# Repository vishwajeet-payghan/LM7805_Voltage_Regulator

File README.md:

**LM7805 5V Voltage Regulator PCB**

A compact PCB designed using the LM7805 linear voltage regulator to convert an input DC voltage into a stable, regulated 5V DC output. The board supports an input voltage range of 7V to 35V DC and includes input and output filter capacitors for improved voltage stability.

# Features
- Voltage Regulator: LM7805 (TO-220 package)
- Input Voltage: 7V–35V DC
- Output Voltage: Fixed 5V DC
- Input Capacitors: 0.1µF and 10µF
- Output Capacitors: 0.1µF and 10µF
- Thermal Management: Dedicated heatsink mounting provision
- PCB Dimensions: 33.23 mm × 41.19 mm
- Input/Output: 2-pin connectors for easy interfacing

# Applications
- Power supply for microcontrollers and embedded systems
- Arduino and other electronics projects
- Low-power 5V DC circuits
- Prototyping and electronics development

# Note
As the LM7805 is a linear regulator, the voltage difference between input and output is dissipated as heat. A suitable heatsink is recommended for higher input voltages or loads with significant current consumption. Ensure the regulator's current and thermal limits are not exceeded.

Designed for compact, simple, and reliable 5V power regulation.

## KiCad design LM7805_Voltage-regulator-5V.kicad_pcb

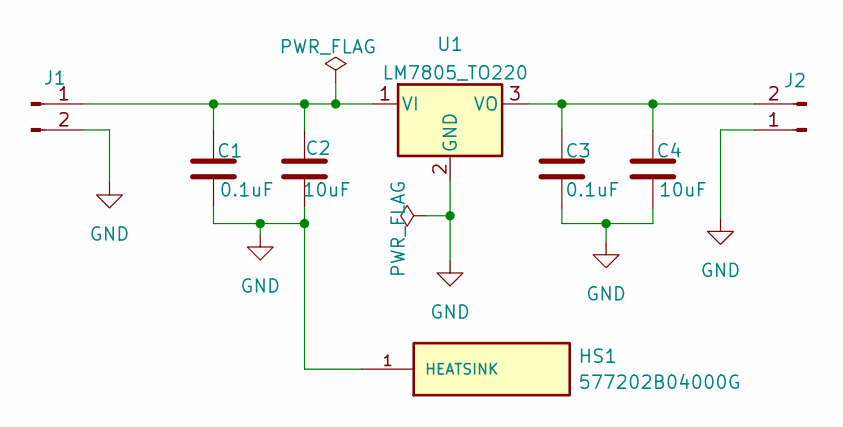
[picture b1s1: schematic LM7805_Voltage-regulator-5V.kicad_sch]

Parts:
C1, C3: 0.1uF; C_0805_2012Metric
C2, C4: 10uF; C_0805_2012Metric
HS1: 577202B04000G; HSINK_577202B04000G; PARTREV NA
J1, J2: Conn_01x02_Pin; PinHeader_1x02_P2.54mm_Vertical
U1: LM7805_TO220; TO-220-3_Vertical

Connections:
GND: C1.2, C2.2, C3.2, C4.2, HS1.1 (HEATSINK_1), J1.2, J2.1, U1.2 (GND)
unnamed: C1.1, C2.1, J1.1, U1.1 (VI)
unnamed: C3.1, C4.1, J2.2, U1.3 (VO)

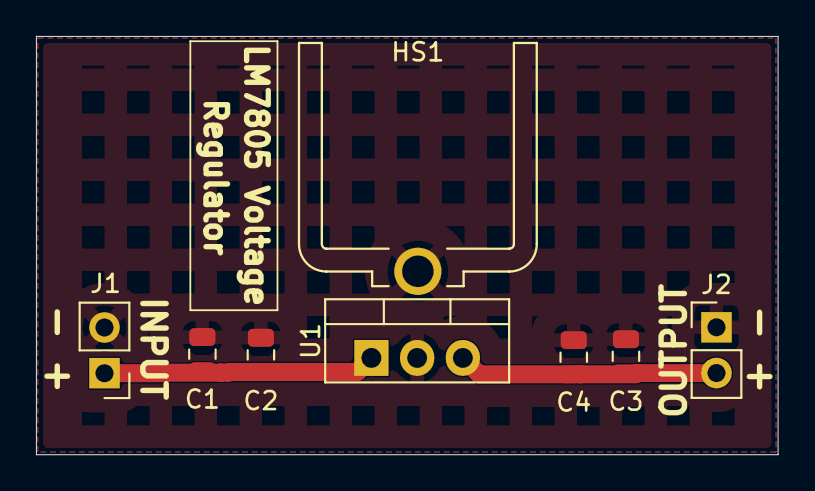
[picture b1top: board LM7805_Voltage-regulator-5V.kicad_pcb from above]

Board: 2 copper layers, 41.2 x 23.2 mm, 8 parts (0 on the bottom side), 3 nets.
